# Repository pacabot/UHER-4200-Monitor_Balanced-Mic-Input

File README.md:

# UHER-4200-Monitor_Balanced-Mic-Input

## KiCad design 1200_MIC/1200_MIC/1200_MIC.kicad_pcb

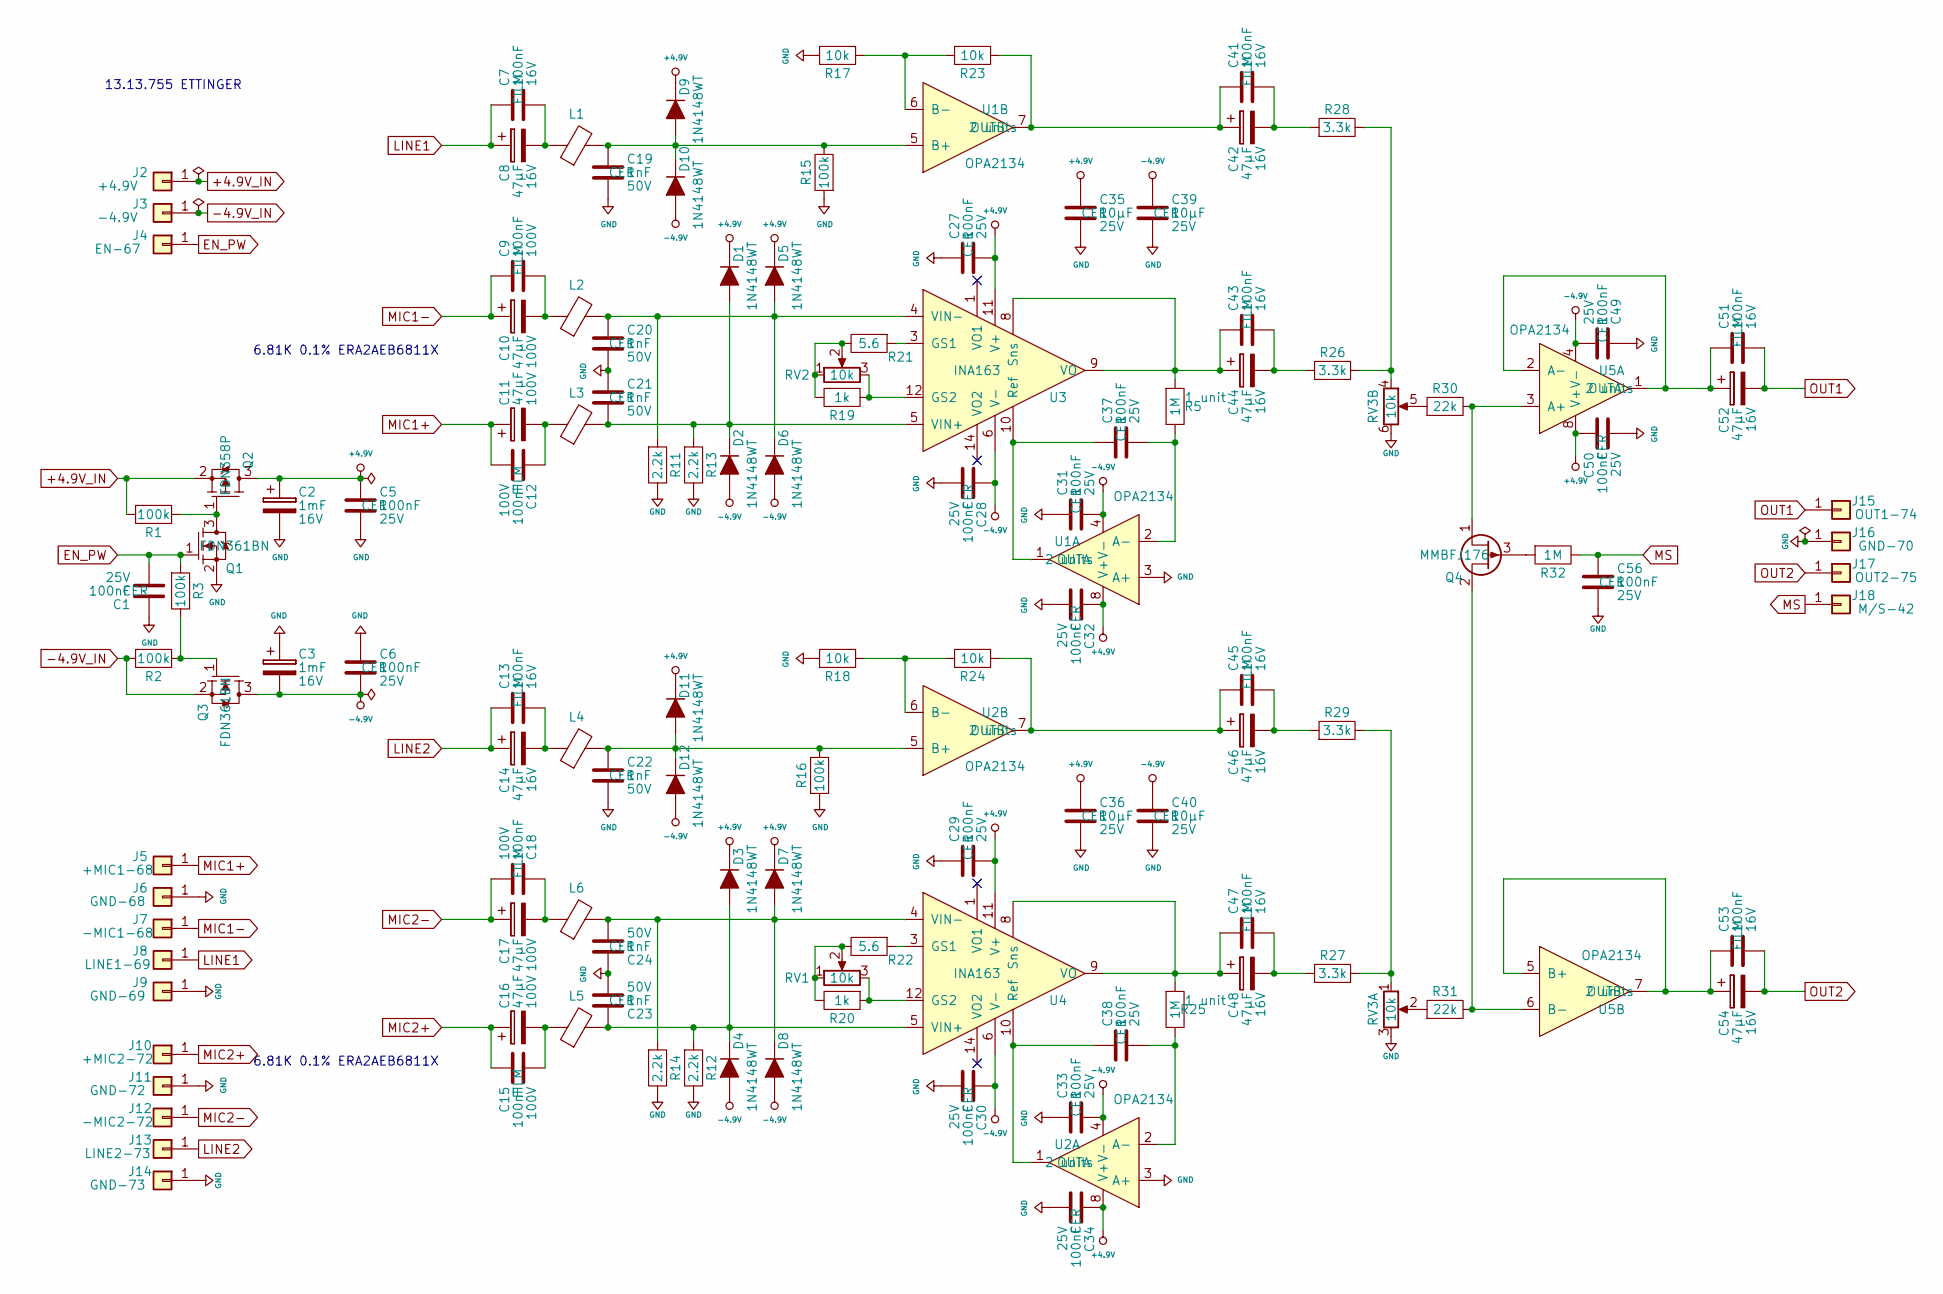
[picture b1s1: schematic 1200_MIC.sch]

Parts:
C1, C5, C6, C27, C28, C29, C30, C31, C32, C33, C34, C37, C38, C49, C50, C56: C_0002; C_0402
C2, C3: C_0077; CP_Radial_D10.0mm_P5.00mm
C7, C13, C41, C43, C45, C47, C51, C53: C_0075; C_0805
C8, C14, C42, C44, C46, C48, C52, C54: C_0078; CP_Radial_D8.0mm_P3.50mm
C9, C12, C15, C18: C_0074; C_2820
C10, C11, C16, C17: C_0072; CP_Radial_D12.5mm_P5.00mm
C19, C20, C21, C22, C23, C24: C_0073; R_0402
C35, C36, C39, C40: C_0005; C_0805
D1, D2, D3, D4, D5, D6, D7, D8, D9, D10, D11, D12: D_0022; D_SOD-523
J2: +4.9V; stamped_contact_2.8mm
J3: -4.9V; stamped_contact_2.8mm
J4: EN-67; stamped_contact_2.8mm
J5: +MIC1-68; stamped_contact_2.8mm
J6: GND-68; stamped_contact_2.8mm
J7: -MIC1-68; stamped_contact_2.8mm
J8: LINE1-69; stamped_contact_2.8mm
J9: GND-69; stamped_contact_2.8mm
J10: +MIC2-72; stamped_contact_2.8mm
J11: GND-72; stamped_contact_2.8mm
J12: -MIC2-72; stamped_contact_2.8mm
J13: LINE2-73; stamped_contact_2.8mm
J14: GND-73; stamped_contact_2.8mm
J15: OUT1-74; stamped_contact_2.8mm
J16: GND-70; stamped_contact_2.8mm
J17: OUT2-75; stamped_contact_2.8mm
J18: M/S-42; stamped_contact_2.8mm
L1, L2, L3, L4, L5, L6: L_0001; LairdTech_28C0236-0JW-10
Q1, Q3: Q_0020; SOT_23
Q2: Q_0019; SOT_23
Q4: Q_0021; SOT_23
R1, R2, R3, R15, R16: R_0034; R_0402
R5, R25, R32: R_0002; R_0402
R11, R12, R13, R14: R_0163; R_0402
R17, R18, R23, R24: R_0020; R_0402
R19, R20: R_0005; R_0402
R21, R22: R_0161; R_0402
R26, R27, R28, R29: R_0164; R_0402
R30, R31: R_0165; R_0402
RV1, RV2: 10k; Potentiometer_Mono_Vertical
RV3: 10k; Potentiometer_Stereo_Vertical
U1, U2, U5: U_0128; SOIC_8
U3, U4: U_0127; SOIC-14_3.9x8.7mm_P1.27mm

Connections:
+4.9V: C2.1, C5.1, C27.2, C29.2, C32.1, C34.1, C35.1, C36.1, C50.1, D1.1 (K), D3.1 (K), D5.1 (K), D7.1 (K), D9.1 (K), D11.1 (K), Q2.3 (D), U1.8 (V+), U2.8 (V+), U3.11 (V+), U4.11 (V+), U5.8 (V+)
+4.9V_IN: J2.1, Q2.2 (S), R1.2
-4.9V: C3.2, C6.2, C28.1, C30.1, C31.2, C33.2, C39.1, C40.1, C49.2, D2.2 (A), D4.2 (A), D6.2 (A), D8.2 (A), D10.2 (A), D12.2 (A), Q3.3 (D), U1.4 (V-), U2.4 (V-), U3.6 (V-), U4.6 (V-), U5.4 (V-)
-4.9V_IN: J3.1, Q3.2 (S), R2.2
EN_PW: C1.2, J4.1, Q1.1 (G), R3.1
GND: C1.1, C2.2, C3.1, C5.2, C6.1, C19.2, C20.2, C21.1, C22.2, C23.2, C24.1, C27.1, C28.2, C29.1, C30.2, C31.1, C32.2, C33.1, C34.2, C35.2, C36.2, C39.2, C40.2, C49.1, C50.2, C56.2, J6.1, J9.1, J11.1, J14.1, J16.1, Q1.2 (S), R11.2, R12.2, R13.2, R14.2, R15.1, R16.1, R17.2, R18.2, RV3.3, RV3.6, U1.3 (A+), U2.3 (A+)
LINE1: C7.1, C8.1, J8.1
LINE2: C13.1, C14.1, J13.1
MIC1+: C11.1, C12.2, J5.1
MIC1-: C9.1, C10.1, J7.1
MIC2+: C15.1, C16.1, J10.1
MIC2-: C17.1, C18.2, J12.1
MS: C56.1, J18.1, R32.2
unnamed: C7.2, C8.2, L1.1
unnamed: C9.2, C10.2, L2.1
unnamed: C11.2, C12.1, L3.1
unnamed: C13.2, C14.2, L4.1
unnamed: C15.2, C16.2, L5.1
unnamed: C17.2, C18.1, L6.1
unnamed: C19.1, D9.2 (A), D10.1 (K), L1.2, R15.2, U1.5 (B+)
unnamed: C20.1, D5.2 (A), D6.1 (K), L2.2, R11.1, U3.4 (VIN-)
unnamed: C21.2, D1.2 (A), D2.1 (K), L3.2, R13.1, U3.5 (VIN+)
unnamed: C22.1, D11.2 (A), D12.1 (K), L4.2, R16.2, U2.5 (B+)
unnamed: C23.1, D3.2 (A), D4.1 (K), L5.2, R12.1, U4.5 (VIN+)
unnamed: C24.2, D7.2 (A), D8.1 (K), L6.2, R14.1, U4.4 (VIN-)
unnamed: C37.1, U1.1 (OUTA), U3.10 (Ref)
unnamed: C37.2, R5.2, U1.2 (A-)
unnamed: C38.1, U2.1 (OUTA), U4.10 (Ref)
unnamed: C38.2, R25.2, U2.2 (A-)
unnamed: C41.1, C42.1, R23.1, U1.7 (OUTB)
unnamed: C41.2, C42.2, R28.1
unnamed: C43.1, C44.1, R5.1, U3.8 (Sns), U3.9 (VO)
unnamed: C43.2, C44.2, R26.1
unnamed: C45.1, C46.1, R24.1, U2.7 (OUTB)
unnamed: C45.2, C46.2, R29.1
unnamed: C47.1, C48.1, R25.1, U4.8 (Sns), U4.9 (VO)
unnamed: C47.2, C48.2, R27.1
unnamed: C51.1, C52.1, U5.1 (OUTA), U5.2 (A-)
unnamed: C53.1, C54.1, U5.5 (B+), U5.7 (OUTB)
unnamed: Q1.3 (D), Q2.1 (G), R1.1
unnamed: Q3.1 (G), R2.1, R3.2
unnamed: Q4.1, R30.2, U5.3 (A+)
unnamed: Q4.2, R31.2, U5.6 (B-)
unnamed: Q4.3, R32.1
unnamed: R17.1, R23.2, U1.6 (B-)
unnamed: R18.1, R24.2, U2.6 (B-)
unnamed: R19.1, RV2.3, U3.12 (GS2)
unnamed: R19.2, R21.2, RV2.1, RV2.2
unnamed: R20.1, RV1.3, U4.12 (GS2)
unnamed: R20.2, R22.2, RV1.1, RV1.2
unnamed: R21.1, U3.3 (GS1)
unnamed: R22.1, U4.3 (GS1)
unnamed: R26.2, R28.2, RV3.4
unnamed: R27.2, R29.2, RV3.1
unnamed: R30.1, RV3.5
unnamed: R31.1, RV3.2
OUT1: C51.2, C52.2, J15.1
OUT2: C53.2, C54.2, J17.1

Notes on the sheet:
6.81K 0.1% ERA2AEB6811X
13.13.755 ETTINGER

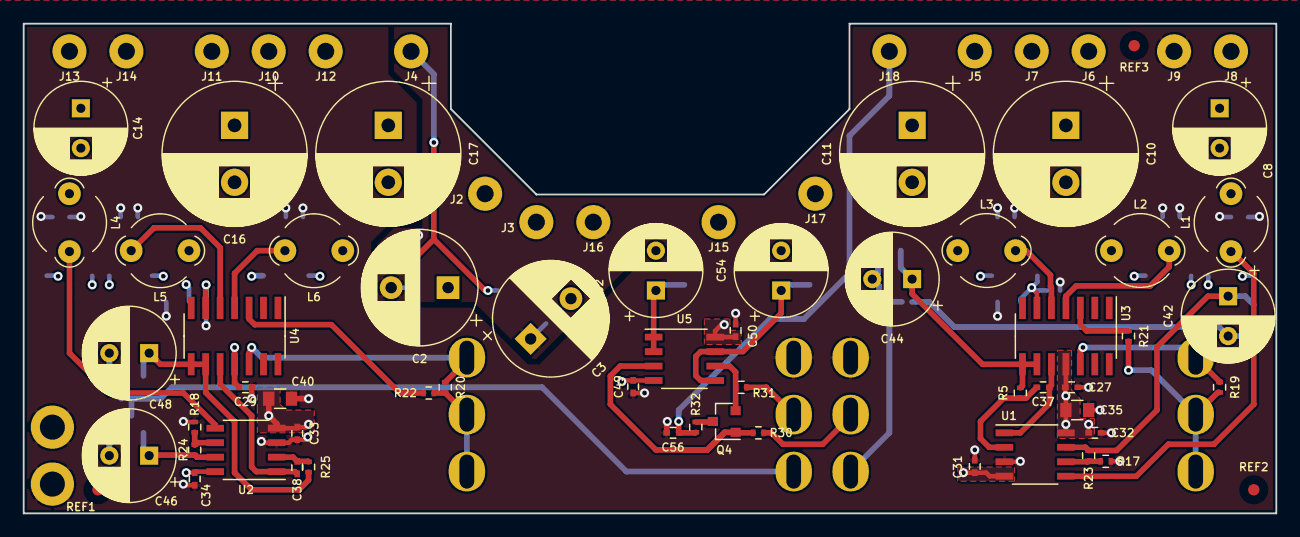
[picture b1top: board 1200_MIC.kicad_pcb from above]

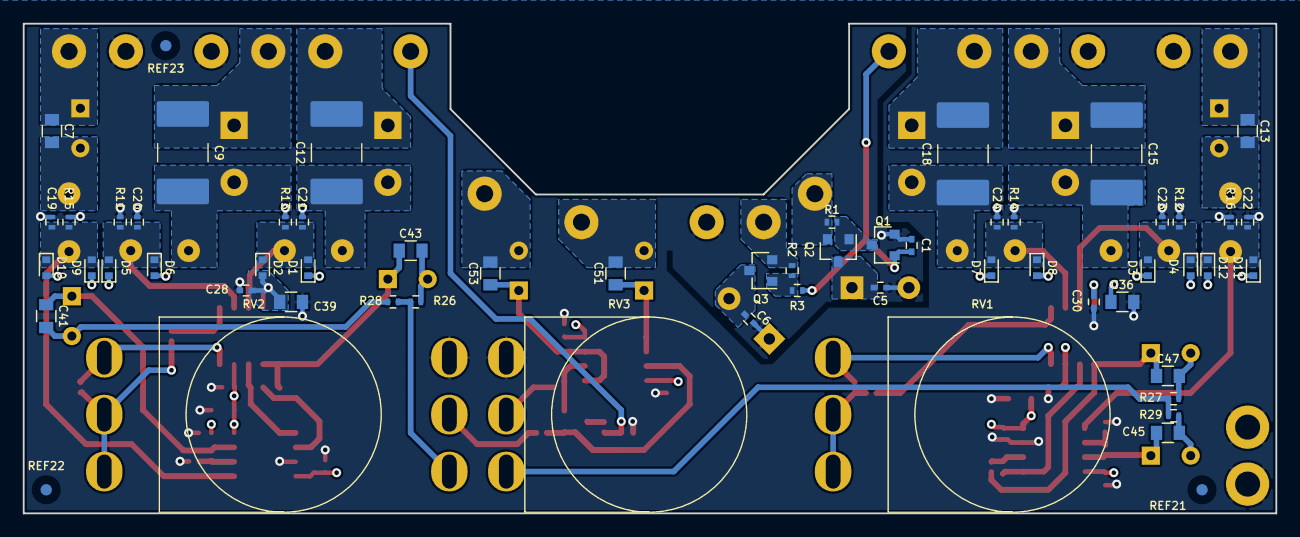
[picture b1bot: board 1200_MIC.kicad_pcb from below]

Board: 4 copper layers, 110.0 x 43.0 mm, 131 parts (59 on the bottom side), 58 nets.

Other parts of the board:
REF1, REF2, REF3, REF21, REF22, REF23: CircleWhite1mm; REF_1mm

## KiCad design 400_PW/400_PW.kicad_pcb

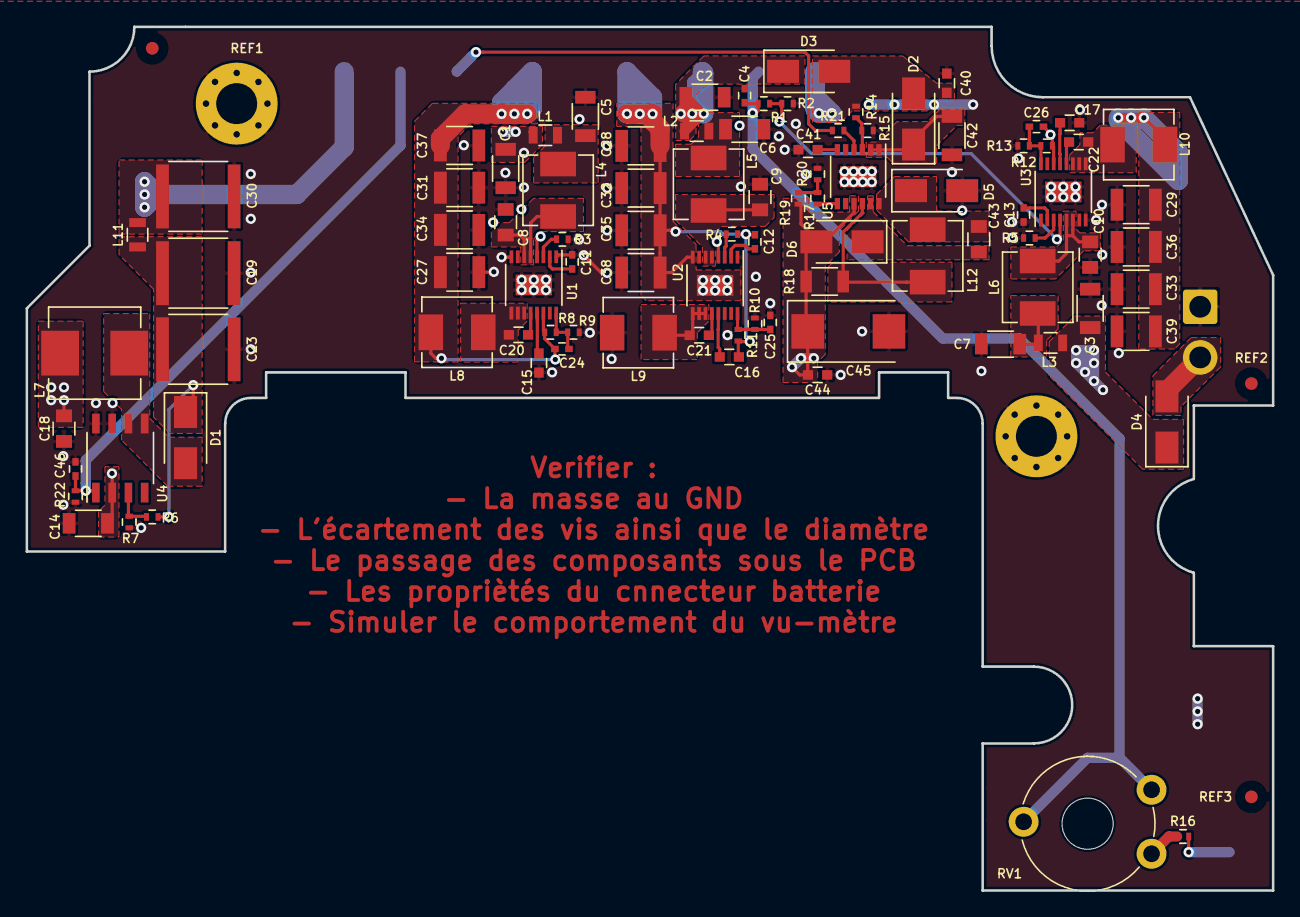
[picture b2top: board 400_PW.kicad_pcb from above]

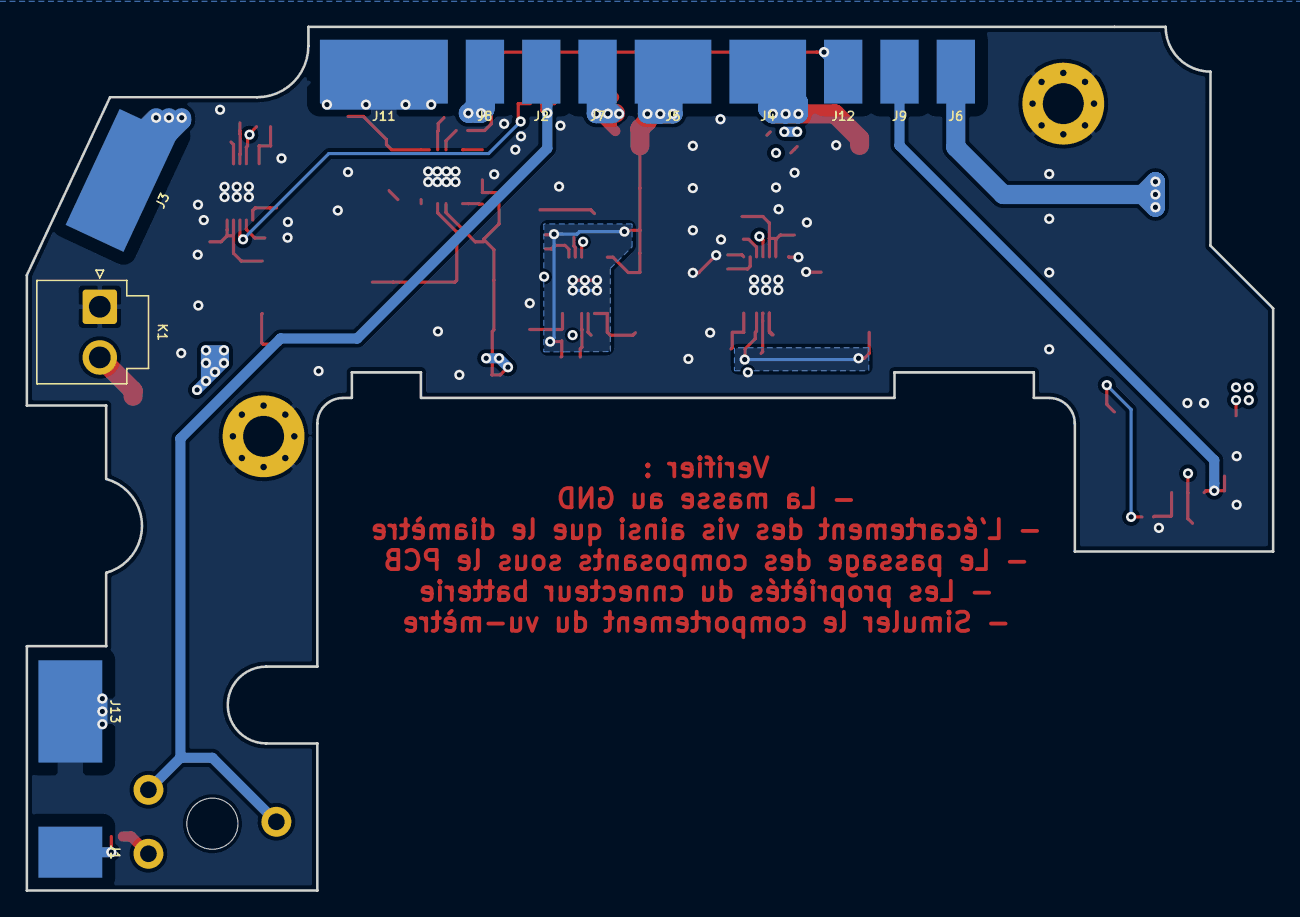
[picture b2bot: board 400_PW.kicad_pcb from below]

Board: 4 copper layers, 97.4 x 67.5 mm, 109 parts (13 on the bottom side), 50 nets.

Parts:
C1, C2, C3, C5, C6, C7, C14: C_0038; C_1206
C4, C11, C12, C13, C46: C_0002; C_0402
C8, C9, C10, C18: C_0032; C_0805
C15, C16, C17, C40: C_0037; C_0603
C19, C23, C30: C_0071; C_2220
C20, C21, C22: C_0012; C_0603
C24, C25, C26: C_0039; C_0402
C27, C28, C29, C31, C32, C33, C34, C35, C36, C37, C38, C39: C_0040; C_1210
C41: C_0057; C_0603
C42: C_0041; C_1206
C43: C_0056; C_0805
C44: C_0003; C_0603
C45: C_0058; CP_EIA-7343-31
D1, D2, D3, D4, D5, D6: D_0026; D_SMA
J1, J12: TESTBAT-14; Solder_Pad_8x5
J2: ON/OFF-6A; Solder_Pad_8x5
J3: +7.5V-13_26_33_51A_54_104_6A; Solder_Pad_8x5
J4: +4.9V-10_36_80_83_93; Solder_Pad_8x5
J5: -4.9V; Solder_Pad_8x5
J6: +48V; Solder_Pad_8x5
J7: ON/OFF-4A_6B; Solder_Pad_8x5
J8: 15VIN-3A; Solder_Pad_8x5
J9: ON/OFF-48V; Solder_Pad_8x5
J11: GND-7_21_22_3B_28_51B_53_76; Solder_Pad_8x5
J13: GND; Solder_Pad_8x5
K1: BATT; JST_VH_B2P-VH_1x02_P3.96mm_Vertical
L1, L2, L3, L11: L_0001; L_0805
L4, L5, L6, L8, L9, L10, L12: L_0004; L_2020-Vishay
L7: L_0015; L_7050-Wurth
R1, R8, R10, R12, R14: R_0002; R_0402
R2: R_0159; R_0402
R3, R4, R5: R_0156; R_0402
R6: R_0154; R_0402
R7: R_0118; R_0402
R9, R11: R_0155; R_0402
R13: R_0158; R_0402
R15: R_0008; R_0402
R16: R_0112; R_0402
R17: R_0128; R_0402
R18: R_0099; R_1206
R19: R_0157; R_0402
R20, R22: R_0034; R_0402
R21: R_0020; R_0402
REF1, REF2, REF3: CircleWhite1mm; REF_1mm
REF1#2: MountingHole_3.2mm_M3_Pad_Via
RV1: 25K; Potentiometer_Piher_PT-10-V10_Vertical_Hole
U1, U2, U3: U_0064; MSOP_16-1EP_3x4_P0.5
U4: U_0126; SOIC_8
U5: U_0089; MSOP_12-1EP_3x4_P0.65

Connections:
+4.9V: C24.1, C27.1, C31.1, C34.1, C37.1, J4.1, L8.2, R8.1, U1.14
+7.5V: C26.1, C29.1, C33.1, C36.1, C39.1, J3.1, L10.2, R12.1, U1.4, U2.4, U3.14
+15: C40.2, D2.2, D3.2, J8.1, R14.2
+48V: C30.2, J6.1, L11.2
+BATT: C44.1, C45.1, D4.2, D6.2, K1.2, R18.1, R19.1, U5.9
-4.9V: C12.2, C16.2, C28.2, C32.2, C35.2, C38.2, J5.1, R4.2, R11.2, U2.8, U2.17
/CHG_LED: J12.1, R21.2
/EN_48V: C46.2, J9.1, R22.1, U4.1
/PW_EN: C4.2, J2.1, R1.2, RV1.1, RV1.2
GND: C1.1, C2.1, C3.1, C4.1, C5.2, C6.2, C7.2, C8.2, C9.2, C10.2, C11.2, C13.2, C14.2, C15.2, C17.2, C18.2, C19.1, C23.1, C25.1, C27.2, C28.1, C29.2, C30.1, C31.2, C32.1, C33.2, C34.2, C35.1, C36.2, C37.2, C38.1, C39.2, C40.1, C41.2, C42.2, C44.2, C45.2, C46.1, D5.2, J11.1, J13.1, K1.1, L9.2, R2.2, R3.2, R5.2, R7.2, R9.2, R10.1, R13.1, R15.1, R20.2, R22.2, REF1#2.1, U1.1, U1.8, U1.17, U2.1, U2.14, U3.1, U3.8, U3.17, U4.7, U4.8, U5.13
unnamed: C5.1, L1.2, L4.1
unnamed: C6.1, L2.2, L5.1
unnamed: C7.1, L3.2, L6.1
unnamed: C8.1, L4.2, U1.5, U1.6
unnamed: C9.1, L5.2, U2.5, U2.6
unnamed: C10.1, L6.2, U3.5, U3.6
unnamed: C11.1, U1.2
unnamed: C12.1, U2.2
unnamed: C13.1, U3.2
unnamed: C15.1, U1.13
unnamed: C16.1, U2.13
unnamed: C17.1, U3.13
unnamed: C19.2, C23.2, D1.1, L11.1, R6.1
unnamed: C20.1, U1.12
unnamed: C20.2, L8.1, U1.9, U1.10, U1.11
unnamed: C21.1, U2.12
unnamed: C21.2, L9.1, U2.9, U2.10, U2.11
unnamed: C22.1, U3.12
unnamed: C22.2, L10.1, U3.9, U3.10, U3.11
unnamed: C24.2, R8.2, R9.1, U1.16
unnamed: C25.2, R10.2, R11.1, U2.16
unnamed: C26.2, R12.2, R13.2, U3.16
unnamed: C41.1, U5.6
unnamed: C42.1, D2.1, U5.1, U5.2
unnamed: C43.1, D5.1, L12.1, U5.12
unnamed: C43.2, D6.1, U5.11
unnamed: D1.2, L7.2, U4.5, U4.6
unnamed: J1.1, R16.1
unnamed: L12.2, R18.2, U5.10
unnamed: R1.1, R2.1, U3.4
unnamed: R3.1, U1.3
unnamed: R4.1, U2.3
unnamed: R5.1, U3.3
unnamed: R6.2, R7.1, U4.3
unnamed: R14.1, R15.2, U5.3
unnamed: R16.2, RV1.3
unnamed: R17.1, R19.2, R20.1
unnamed: R17.2, U5.7
unnamed: R21.1, U5.4
VDD: C1.2, C2.2, C3.2, C14.1, C18.1, D3.1, D4.1, J7.1, L1.1, L2.1, L3.1, L7.1, U4.2

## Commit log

2019-10-21 Add documentations
2019-10-28 Update 400_PW schematics
2019-10-29 Update schematics
2019-11-01 Place components on 400_PW
2019-11-02 Update PW 400
2019-12-05 Add 1200_MIC schematic
2019-12-15 First version preamp 1200
2019-12-31 600 MIC v1.0.0
